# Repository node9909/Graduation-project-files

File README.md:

# Graduation internship report attachments (HD-SEMG system ADS1298)
 THis folder includes: Hardware files, software files, python application, MATLAB and report, design was to build a protable and wireless HD-SEMG aquisition system for my graduation internship of my electrical engineering degree at Hogeschool Rotterdam, the internship took place at Bio-engineering.pl in Wroclaw.

 The hypothesis of the project was ”Can the AMAC performance level be improved in direct controlled (DC) myoelectric systems by exactly locating the location where the patient has the most amount of cover the agonist and antagonist of the residual limb during different hand gestures’’. The goal was to develop a device that can be used to confirm this hypothesis, the could be achieved by measuring the muscle potentials over the residual limb during different hand gestures (HD-SEMG recording)

 In the project multiple AFE were designed were presented (based on AD8232 adn INA333), the function of the AFE to amplify and filter the EMG signal. THe EMG channels were digitezed using the ADS1298. the ADC data is read from the ADS1298 via an Arduino DUE (SAM3X8E)/ STM32F4.A PC application was developed to visualize the data and verifiy certain system specification (CMRR, IRN and Gain). The Current design is capable of measuring up to 1kSps with the Arduino DUE and to >4kSps with the STM32F411, the problem with the STM32F4 is the the Python application and realterm cannot open the USB port (CDC) to read the data, but it can be open in Tera term. If anybody knows why I would be happy to know :) 

 If you would like to continue this project Idea, feel to contact me for more info about the future improvements or any other questions about the design of the project.

# Contact details
 If you have any questions about the project feel free to contract me at: okersten@gmail.com

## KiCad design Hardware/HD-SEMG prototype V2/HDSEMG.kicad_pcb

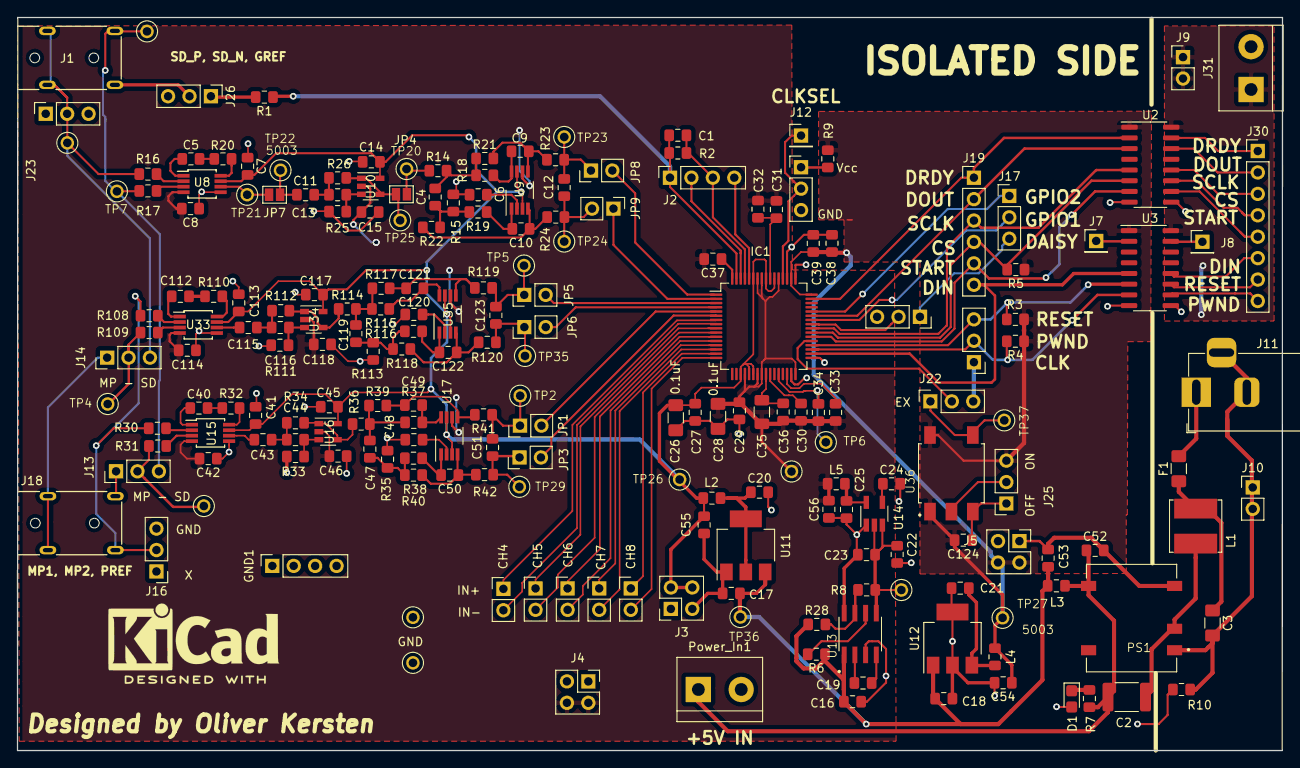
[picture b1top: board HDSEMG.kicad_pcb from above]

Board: 2 copper layers, 150.0 x 86.9 mm, 209 parts (0 on the bottom side), 140 nets.

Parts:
C1: 1M; C_0805_2012Metric_Pad1.15x1.40mm_HandSolder
C2: 470pF; Fuse_1812_4532Metric_Pad1.30x3.40mm_HandSolder
C3: 2.2uF; C_1206_3216Metric_Pad1.42x1.75mm_HandSolder
C4: 47nF; C_0805_2012Metric_Pad1.15x1.40mm_HandSolder
C5, C16, C22, C40, C112: 4.7uF; C_0805_2012Metric_Pad1.15x1.40mm_HandSolder
C6, C48, C120: 220nF; C_0805_2012Metric_Pad1.15x1.40mm_HandSolder
C7, C8, C14, C15, C41, C42, C45, C46, C113, C114, C117, C118: 100n; C_0805_2012Metric_Pad1.15x1.40mm_HandSolder
C9, C10, C50, C122: 2.2nF; C_0805_2012Metric_Pad1.15x1.40mm_HandSolder
C11, C13, C43, C44, C115, C116: 100nF; C_0805_2012Metric_Pad1.15x1.40mm_HandSolder
C12, C51, C123: 33nF; C_0805_2012Metric_Pad1.15x1.40mm_HandSolder
C17, C18, C19, C21, C27, C29, C30, C31, C33, C39: 1uF; C_0805_2012Metric_Pad1.15x1.40mm_HandSolder
C20, C23, C25: 2.2uF; C_0805_2012Metric_Pad1.15x1.40mm_HandSolder
C24, C124: 10nF; C_0805_2012Metric_Pad1.15x1.40mm_HandSolder
C26, C28: 0.1uF; C_1206_3216Metric_Pad1.42x1.75mm_HandSolder
C32: .1uF; C_0805_2012Metric_Pad1.15x1.40mm_HandSolder
C34: 22uF; C_0805_2012Metric_Pad1.15x1.40mm_HandSolder
C35: 10uF; C_1206_3216Metric
C36: 0.1u; C_0805_2012Metric_Pad1.15x1.40mm_HandSolder
C37: 1nF; C_0805_2012Metric_Pad1.15x1.40mm_HandSolder
C38: 0.1uF; C_0805_2012Metric_Pad1.15x1.40mm_HandSolder
C47, C119: 47n; C_0805_2012Metric_Pad1.15x1.40mm_HandSolder
C49, C121: 2.2n; C_0805_2012Metric_Pad1.15x1.40mm_HandSolder
C52, C53, C54, C55, C56: 10uF; C_0805_2012Metric_Pad1.15x1.40mm_HandSolder
CH4, CH5, CH6, CH7, CH8: Conn_01x02; PinHeader_1x02_P2.54mm_Vertical
D1: LED; D_0805_2012Metric_Castellated
F1: Fuse; Fuse_1206_3216Metric_Pad1.42x1.75mm_HandSolder
GND1: Conn_02x02_Counter_Clockwise; PinSocket_1x04_P2.54mm_Vertical
IC1: ADS1298_By_Oliver; TQFP-64_10x10mm_P0.5mm
J1, J18: AUDIO_JACK_By_OLIVER; MX387GL
J2: Conn_01x04; PinSocket_1x04_P2.54mm_Vertical
J3, J4, J5: Conn_02x02_Counter_Clockwise; PinSocket_2x02_P2.54mm_Vertical
J7, J8, J12: Conn_01x01; PinHeader_1x01_P2.54mm_Vertical
J9, J10: Conn_01x02; PinHeader_1x02_P2.54mm_Vertical
J11: Barrel_Jack_Switch; BarrelJack_Horizontal
J13, J14, J15, J16, J17, J24, J26: Conn_01x03; PinHeader_1x03_P2.54mm_Vertical
J19: Conn_01x06; PinHeader_1x06_P2.54mm_Vertical
J21, J22, J23, J25: Conn_01x03; PinSocket_1x03_P2.54mm_Vertical
J30: Conn_01x08; PinHeader_1x08_P2.54mm_Vertical
J31: Screw_Terminal_01x02; TerminalBlock_bornier-2_P5.08mm
JP1, JP3, JP5, JP6, JP8, JP9: Jumper; PinHeader_1x02_P2.54mm_Vertical
JP4, JP7: Jumper; SolderJumper-2_P1.3mm_Open_Pad1.0x1.5mm
L1: 10uH; L_Bourns_SRN6045TA
L2, L3, L4, L5: INDUCTOR; L_0805_2012Metric_Pad1.15x1.40mm_HandSolder
PS1: R2S-1205; CONV_R2S-1205
Power_In1: Screw_Terminal_01x02; TerminalBlock_bornier-2_P5.08mm
R1, R28: 100k; R_0805_2012Metric_Pad1.15x1.40mm_HandSolder
R2: 1.5nF; R_0805_2012Metric_Pad1.15x1.40mm_HandSolder
R3, R4, R5: 10K; R_0805_2012Metric_Pad1.15x1.40mm_HandSolder
R6, R7, R9: 10k; R_0805_2012Metric_Pad1.15x1.40mm_HandSolder
R8: 50k; R_0805_2012Metric_Pad1.15x1.40mm_HandSolder
R10: 0R; R_0805_2012Metric_Pad1.15x1.40mm_HandSolder
R14, R15, R35, R36, R113, R114: 1.1k; R_0805_2012Metric_Pad1.15x1.40mm_HandSolder
R16, R17, R30, R31, R108, R109: 51k; R_0805_2012Metric_Pad1.15x1.40mm_HandSolder
R18, R19, R37, R38, R115, R116: 5.6k; R_0805_2012Metric_Pad1.15x1.40mm_HandSolder
R20, R32, R110: 4300R; R_0805_2012Metric_Pad1.15x1.40mm_HandSolder
R21, R22, R39, R40, R117, R118: 11k; R_0805_2012Metric_Pad1.15x1.40mm_HandSolder
R23, R24, R41, R42, R119, R120: 50R; R_0805_2012Metric_Pad1.15x1.40mm_HandSolder
R25, R34, R112: 220k; R_0805_2012Metric_Pad1.15x1.40mm_HandSolder
R26: 110k; R_0805_2012Metric_Pad1.15x1.40mm_HandSolder
R33, R111: 430k; R_0805_2012Metric_Pad1.15x1.40mm_HandSolder
TP1, TP3, TP4, TP6, TP7, TP11, TP12, TP13, TP14, TP20, TP21, TP22, TP23, TP24, TP25, TP26, TP27, TP28, TP29, TP35, TP36, TP37: 5003; keystone_PCB_TEST_PIN
TP2, TP5: 5003; TPCW51D250H460P
U2, U3: Si8663; SOIC-16_3.9x9.9mm_P1.27mm
U8, U15, U33: INA333AIDGKR; MSOP-8_3x3mm_P0.65mm
U9, U17, U35: THS4521IDGKT; VSSOP-8_3.0x3.0mm_P0.65mm
U10, U16, U34: OPA333xxDBV; SOT-23-5
U11: TLV1117-25; SOT-223-3_TabPin2
U12: MCP1825S; SOT-223-3_TabPin2
U13: MAX889TESA+; SOIC127P600X175-8N
U14: TPS72325; SOT-23-5_HandSoldering
U36: 357LB3CI002M0480; SOIC254P1016X460-5N

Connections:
+2V5: C7.2, C14.1, C26.1, C27.1, C41.2, C45.1, C55.1, C113.2, C117.1, IC1.19, IC1.21, IC1.22, IC1.54, IC1.56, IC1.59, J3.3, J3.4, L2.2, TP26.1, U8.7, U9.3, U9.7, U10.5, U15.7, U16.5, U17.3, U17.7, U33.7, U34.5, U35.3, U35.7
+3V3: J9.1, J9.2, J31.1, U2.16, U3.16
+3_3V: C38.1, C39.1, C54.1, C124.2, IC1.48, IC1.50, J5.3, J5.4, J25.3, L4.2, R3.1, R4.1, R5.1, R9.1, TP27.1, U2.1, U3.1, U36.1, U36.6
+5V: C2.1, C52.1, L3.2, PS1.5, Power_In1.1, R7.1
-2V5: C8.2, C15.1, C28.1, C29.1, C30.2, C31.2, C32.2, C33.2, C34.2, C35.2, C36.2, C37.2, C42.2, C46.1, C56.1, C114.2, C118.1, IC1.20, IC1.23, IC1.24, IC1.32, IC1.53, IC1.57, IC1.58, J4.3, J4.4, L5.2, TP28.1, U8.4, U9.6, U10.2, U15.4, U16.2, U17.6, U33.4, U34.2, U35.6
/ADS1298 AFE in DUE out/EX_CLK_SIG: J22.1, TP37.1, U36.4
/Alternative Desing 1.3/low_pass_out: JP4.1, R26.1, TP25.1, U10.1, U10.4
/Input two/IN+3: J13.2, R31.2, TP3.1
/Power supply circuit/Power_IN: C16.1, C17.1, C18.1, C53.1, L3.1, R6.1, R28.1, TP36.1, U11.3, U12.1, U13.1
/sheet5DE654DA/IN+3: J14.2, R109.2, TP4.1
CHA_SD: J1.3, J13.3, R17.2, TP7.1, TP11.1
CHA_SD_N: J1.2, J14.3, J23.2, R16.2, TP12.1
CHB_MP: J14.1, J18.2
CHC_MP: J13.1, J18.3
CLK: J15.1, J22.3
CLKSEL: IC1.52, J12.1, J24.2
CS: IC1.39, J19.4, R5.2, U2.6
DAISY_CON_1: J17.3, J21.1
DGND: C6.2, C7.1, C8.1, C14.2, C15.2, C16.2, C17.2, C18.2, C20.2, C21.2, C22.2, C23.2, C24.2, C25.2, C26.2, C27.2, C28.2, C29.2, C38.2, C39.2, C41.1, C42.1, C45.2, C46.2, C48.2, C52.2, C53.2, C54.2, C55.2, C56.2, C113.1, C114.1, C117.2, C118.2, C120.2, C124.1, D1.2, GND1.1, GND1.2, GND1.3, GND1.4, IC1.31, IC1.33, IC1.49, IC1.51, J3.1, J3.2, J4.1, J4.2, J5.1, J5.2, J16.3, J21.3, J23.3, J24.3, J25.1, J26.3, PS1.4, Power_In1.2, R10.2, R15.1, R25.1, R33.1, R35.1, R111.1, R113.1, TP13.1, TP14.1, U2.8, U3.8, U8.5, U11.1, U12.2, U13.3, U13.8, U14.1, U15.5, U33.5, U36.3
DIN: IC1.34, J19.6, U3.5
DOUT: IC1.43, J19.2, U2.3
DRDY: IC1.47, J19.1, U2.2
GNDA: C3.2, J10.1, J10.2, J11.2, J11.3, J31.2, PS1.1, R10.1, U2.9, U3.9
GPIO_1: IC1.42, J17.2
GPIO_2: IC1.44, J17.1
IN1N: IC1.2, JP9.1
IN1P: IC1.1, JP8.2
IN2N: IC1.4, JP6.2
IN2P: IC1.3, JP5.2
IN3N: IC1.6, JP3.2
IN3P: IC1.5, JP1.2
IN4N: CH4.2, IC1.8
IN4P: CH4.1, IC1.7
IN5N: CH5.2, IC1.10
IN5P: CH5.1, IC1.9
IN6N: CH6.2, IC1.12
IN6P: CH6.1, IC1.11
IN7N: CH7.2, IC1.14
IN7P: CH7.1, IC1.13
IN8N: CH8.2, IC1.16
IN8P: CH8.1, IC1.15
ISO_CS: J30.4, U2.11
ISO_DIN: J30.6, U3.12
ISO_DOUT: J30.2, U2.14
ISO_DRDY: J30.1, U2.15
ISO_PWDN: J30.8, U3.10
ISO_RESET: J30.7, U3.11
ISO_SCLK: J30.3, U2.12
ISO_START: J30.5, U2.10
unnamed: C2.2, L1.2, PS1.2
unnamed: C3.1, F1.1, L1.1
unnamed: C4.1, R15.2, R19.1, R22.1
unnamed: C4.2, R14.2, R18.1, R21.1
unnamed: C5.1, U8.1
unnamed: C5.2, R20.2
unnamed: C6.1, U9.2
unnamed: C9.1, R21.2, R23.2, U9.5
unnamed: C9.2, R18.2, U9.8
unnamed: C10.1, R22.2, R24.1, U9.4
unnamed: C10.2, R19.2, U9.1
unnamed: C11.1, JP7.2, TP22.1
unnamed: C11.2, C13.1, R26.2
unnamed: C12.1, JP8.1, R23.1, TP23.1
unnamed: C12.2, JP9.2, R24.2, TP24.1
unnamed: C13.2, R25.2, U10.3
unnamed: C19.1, U13.2
unnamed: C19.2, U13.4
unnamed: C20.1, L2.1, U11.2
unnamed: C21.1, L4.1, U12.3
unnamed: C22.1, C23.1, R8.1, TP1.1, U13.5, U14.2, U14.3
unnamed: C24.1, U14.4
unnamed: C25.1, L5.1, U14.5
unnamed: C40.1, U15.1
unnamed: C40.2, R32.2
unnamed: C43.1, U15.6
unnamed: C43.2, C44.1, R34.2
unnamed: C44.2, R33.2, U16.3
unnamed: C47.1, R35.2, R38.1, R40.1
unnamed: C47.2, R36.2, R37.1, R39.1
unnamed: C48.1, U17.2
unnamed: C49.1, R39.2, R41.2, U17.5
unnamed: C49.2, R37.2, U17.8
unnamed: C50.1, R40.2, R42.1, U17.4
unnamed: C50.2, R38.2, U17.1
unnamed: C51.1, JP1.1, R41.1, TP2.1
unnamed: C51.2, JP3.1, R42.2, TP29.1
unnamed: C112.1, U33.1
unnamed: C112.2, R110.2
unnamed: C115.1, U33.6
unnamed: C115.2, C116.1, R112.2
unnamed: C116.2, R111.2, U34.3
unnamed: C119.1, R113.2, R116.1, R118.1
unnamed: C119.2, R114.2, R115.1, R117.1
unnamed: C120.1, U35.2
unnamed: C121.1, R117.2, R119.2, U35.5
unnamed: C121.2, R115.2, U35.8
unnamed: C122.1, R118.2, R120.1, U35.4
unnamed: C122.2, R116.2, U35.1
unnamed: C123.1, JP5.1, R119.1, TP5.1
unnamed: C123.2, JP6.1, R120.2, TP35.1
unnamed: D1.1, R7.2
unnamed: F1.2, J11.1
unnamed: IC1.37, J22.2
unnamed: IC1.41, J21.2
unnamed: J1.1, J26.2
unnamed: J7.1, U3.2
unnamed: J8.1, U3.15
unnamed: J24.1, R9.2
unnamed: J25.2, U36.2
unnamed: J26.1, R1.2
unnamed: JP4.2, R14.1, TP20.1
unnamed: JP7.1, TP21.1, U8.6
unnamed: R6.2, U13.6
unnamed: R16.1, U8.2
unnamed: R17.1, U8.3
unnamed: R20.1, U8.8
unnamed: R8.2, R28.2, U13.7
unnamed: R30.1, U15.2
unnamed: R31.1, U15.3
unnamed: R32.1, U15.8
unnamed: R34.1, R36.1, U16.1, U16.4
unnamed: R108.1, U33.2
unnamed: R109.1, U33.3
unnamed: R110.1, U33.8
unnamed: R112.1, R114.1, U34.1, U34.4
PREF: J16.2, J18.1, R30.2, R108.2
PWDN: IC1.35, J15.2, R4.2, U3.7
RESET: IC1.36, J15.3, R3.2, U3.6
RLDIN1: IC1.62, J2.2
RLDINV: C1.2, IC1.61, J2.3, R2.1
RLDOUT1: C1.1, IC1.63, J2.1, R1.1, R2.2
RLD_REF1: IC1.60, J2.4
SCLK: IC1.40, J19.3, U2.5
START: IC1.38, J19.5, U2.7
VCAP1_1: C34.1, IC1.28, TP6.1
VCAP2_1: C33.1, IC1.30
VCAP3_1: C31.1, C32.1, IC1.55
VCAP4_1: C30.1, IC1.26
VREFP1: C35.1, C36.1, IC1.25
WTC_1: C37.1, IC1.64

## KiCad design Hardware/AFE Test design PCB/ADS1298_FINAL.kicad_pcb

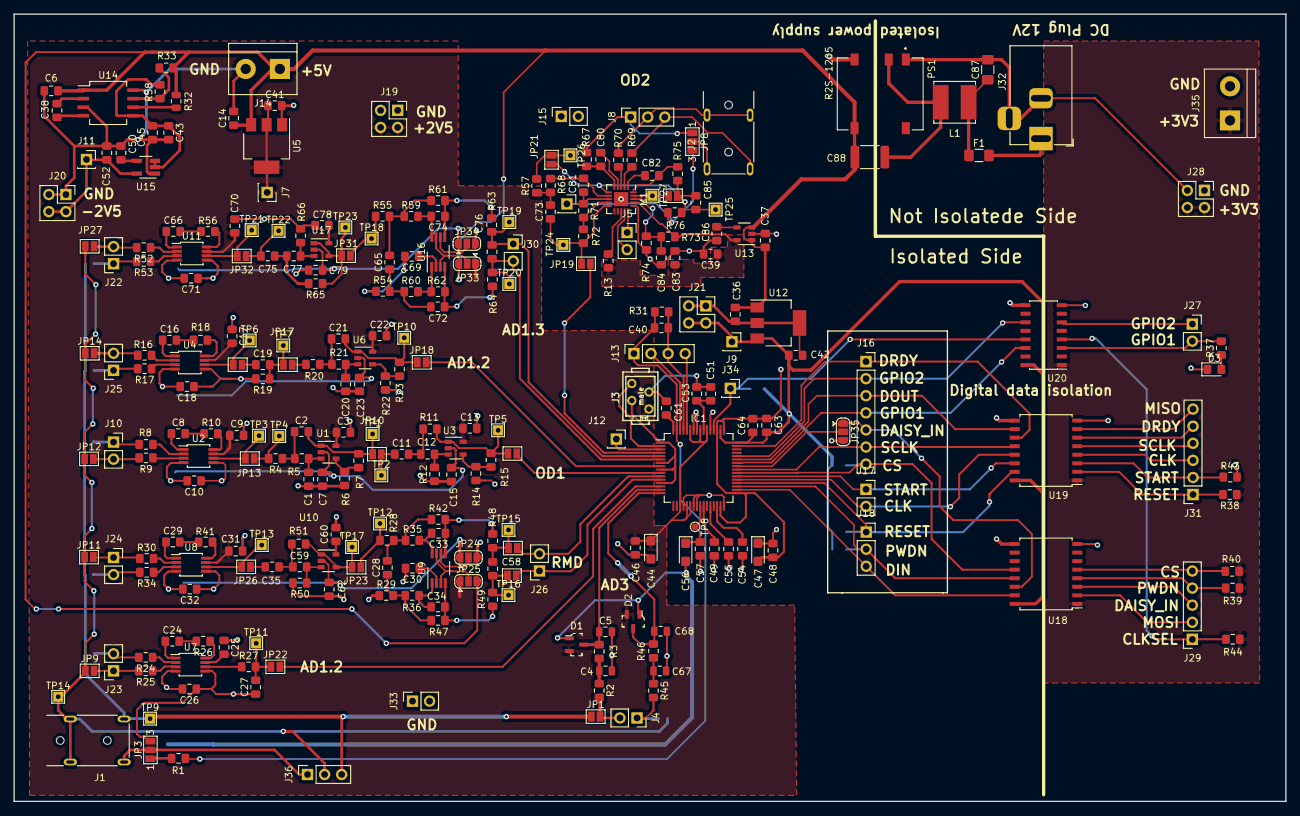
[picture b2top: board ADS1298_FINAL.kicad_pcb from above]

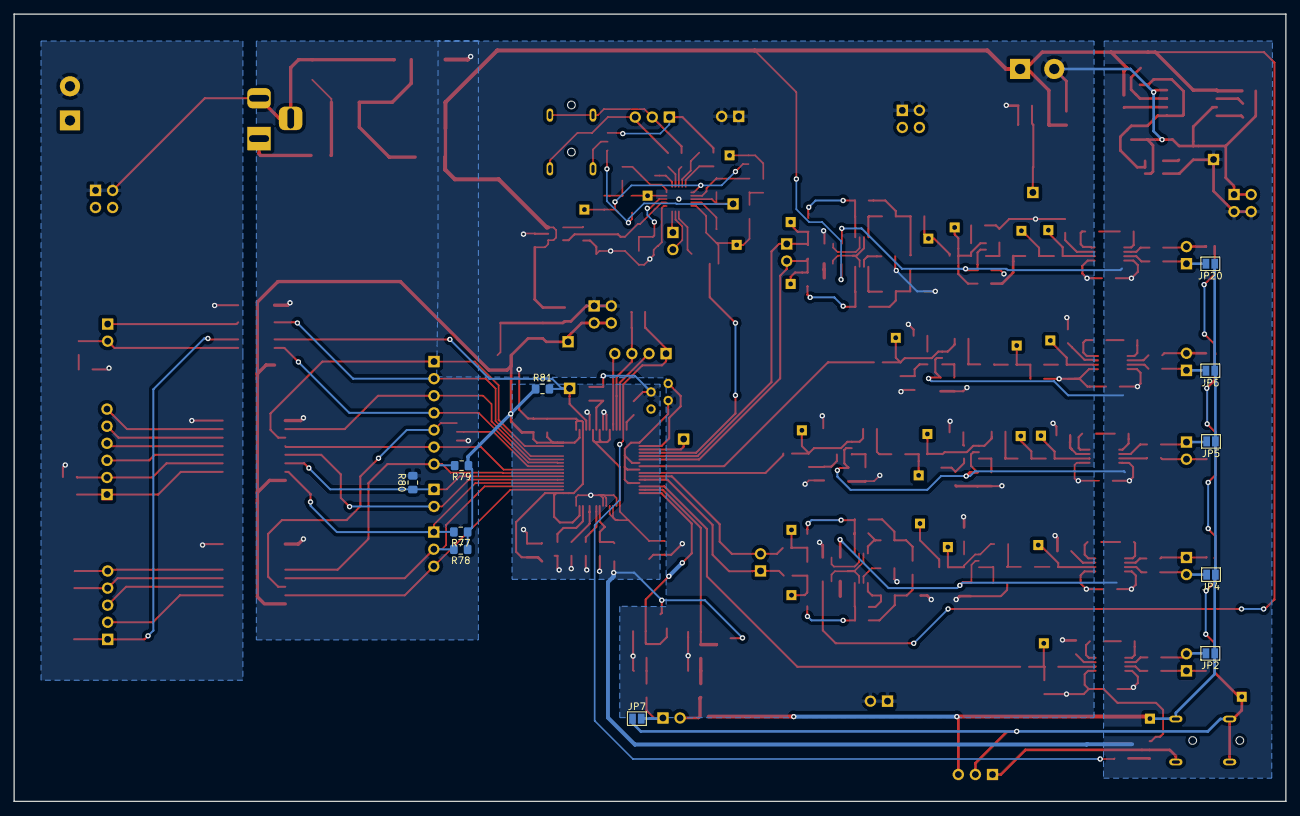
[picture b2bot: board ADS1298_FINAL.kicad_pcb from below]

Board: 2 copper layers, 189.0 x 117.0 mm, 295 parts (11 on the bottom side), 187 nets.

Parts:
C1, C2, C20, C21, C35, C59, C75, C77: 4.7nF; C_0805_2012Metric_Pad1.15x1.40mm_HandSolder
C3, C7, C9, C10, C13, C15, C17, C18, C19, C22, C23, C25, C26, C27, C28, C30, C31, C32, C33, C34, C58, C60, C62, C65, C69, C70, C71, C72, C74, C76, C78, C79: 100n; C_0805_2012Metric_Pad1.15x1.40mm_HandSolder
C4, C5, C67, C68: 47pF; C_0805_2012Metric
C6, C43: 4.7uF; C_0805_2012Metric_Pad1.15x1.40mm_HandSolder
C8, C16, C24, C29: 10uF; C_0805_2012Metric_Pad1.15x1.40mm_HandSolder
C11, C12, C50, C86: 10nF; C_0805_2012Metric_Pad1.15x1.40mm_HandSolder
C14, C36, C37, C38, C41, C42, C49, C51, C54, C64, C66: 1uF; C_0805_2012Metric_Pad1.15x1.40mm_HandSolder
C39, C45, C52: 2.2uF; C_0805_2012Metric_Pad1.15x1.40mm_HandSolder
C40: 1M; C_0805_2012Metric_Pad1.15x1.40mm_HandSolder
C44: 10uF; CP_EIA-3216-12_Kemet-S
C46, C48, C57: 0.1u; C_0805_2012Metric_Pad1.15x1.40mm_HandSolder
C47, C56: 10uF; CP_EIA-3216-10_Kemet-I
C53: .1uF; C_0805_2012Metric_Pad1.15x1.40mm_HandSolder
C55: 22uF; C_0805_2012Metric_Pad1.15x1.40mm_HandSolder
C61, C73, C80, C81: 1nF; C_0805_2012Metric_Pad1.15x1.40mm_HandSolder
C63: 0.1uF; C_0805_2012Metric_Pad1.15x1.40mm_HandSolder
C82, C85: 4700nF; C_0805_2012Metric_Pad1.15x1.40mm_HandSolder
C83, C84: 100nF; C_0805_2012Metric_Pad1.15x1.40mm_HandSolder
C87: 2.2uF; C_1206_3216Metric_Pad1.42x1.75mm_HandSolder
C88: 470pF; Fuse_1812_4532Metric_Pad1.30x3.40mm_HandSolder
D1, D2: D_Schottky_x2_Serial_AKC; SOT-23-3
D3: LED; LED_0805_2012Metric_Pad1.15x1.40mm_HandSolder
F1: Fuse; Fuse_1206_3216Metric_Pad1.42x1.75mm_HandSolder
IC1: ADS1298_By_Oliver; TQFP-64_10x10mm_P0.5mm
J1, J2: AUDIO_JACK_By_OLIVER; MX387GL
J3: external header 2; 0-215464-4_TH_4-pin_male
J4, J5, J10, J15, J17, J22, J23, J24, J25, J26, J27, J30, J33: Conn_01x02; PinSocket_1x02_P2.54mm_Vertical
J6, J7, J9, J11, J12, J34: Conn_01x01; PinSocket_1x01_P2.54mm_Vertical
J8, J18, J36: Conn_01x03; PinSocket_1x03_P2.54mm_Vertical
J13: Conn_01x04; PinSocket_1x04_P2.54mm_Vertical
J14, J35: Screw_Terminal_01x02; TerminalBlock_bornier-2_P5.08mm
J16: Conn_01x07; PinSocket_1x07_P2.54mm_Vertical
J19, J20, J21, J28: Conn_02x02_Counter_Clockwise; PinSocket_2x02_P2.54mm_Vertical
J29: Conn_01x05; PinSocket_1x05_P2.54mm_Vertical
J31: Conn_01x06; PinSocket_1x06_P2.54mm_Vertical
J32: Barrel_Jack_Switch; BarrelJack_Horizontal
JP1, JP2, JP4, JP5, JP6, JP7, JP9, JP11, JP12, JP14, JP19, JP20, JP27: SolderJumper_2_Open; SolderJumper-2_P1.3mm_Open_Pad1.0x1.5mm
JP3, JP8: Jumper_3_Open; SolderJumper-3_P1.3mm_Open_Pad1.0x1.5mm_NumberLabels
JP10, JP13, JP15, JP16, JP17, JP18, JP22, JP23, JP26, JP28, JP30, JP31, JP32: Jumper; SolderJumper-2_P1.3mm_Open_Pad1.0x1.5mm
JP21, JP29: Jumper_2_Open; SolderJumper-2_P1.3mm_Open_Pad1.0x1.5mm
JP24, JP25, JP33, JP34, JP35: Jumper_3_Open; SolderJumper-3_P1.3mm_Open_RoundedPad1.0x1.5mm
L1: 10uH; L_Bourns_SRN6045TA
M1: AD8232; LFCSP-20-1EP_4x4mm_P0.5mm_EP2.1x2.1mm
PS1: R2S-1205; CONV_R2S-1205
R1, R8, R9, R16, R17, R24, R25, R30, R33, R34, R52, R53: 100k; R_0805_2012Metric_Pad1.15x1.40mm_HandSolder
R2, R3, R45, R46: 2.1k; R_0805_2012Metric_Pad1.15x1.40mm_HandSolder
R4: 47k; R_0805_2012Metric_Pad1.15x1.40mm_HandSolder
R5: 91k; R_0805_2012Metric_Pad1.15x1.40mm_HandSolder
R6, R39, R78: 10K; R_0805_2012Metric_Pad1.15x1.40mm_HandSolder
R7, R13, R14, R15, R22, R38, R43, R44, R71, R77, R80, R81: 10k; R_0805_2012Metric_Pad1.15x1.40mm_HandSolder
R10, R18, R26, R41: 1300R; R_0805_2012Metric_Pad1.15x1.40mm_HandSolder
R11: 1.8M; R_0805_2012Metric_Pad1.15x1.40mm_HandSolder
R12: 1.3M; R_0805_2012Metric_Pad1.15x1.40mm_HandSolder
R19, R27, R37: 1K; R_0805_2012Metric_Pad1.15x1.40mm_HandSolder
R20, R50: 36k; R_0805_2012Metric_Pad1.15x1.40mm_HandSolder
R21, R28, R29, R35, R36, R42, R47, R48, R49, R51, R54, R55, R59, R60, R61, R62, R63, R64: 130k; R_0805_2012Metric_Pad1.15x1.40mm_HandSolder
R23, R72: 30k; R_0805_2012Metric_Pad1.15x1.40mm_HandSolder
R31: 1.5nF; R_0805_2012Metric_Pad1.15x1.40mm_HandSolder
R32: 10k; R_0805_2012Metric
R40, R79: 100K; R_0805_2012Metric_Pad1.15x1.40mm_HandSolder
R56: 20k; R_0805_2012Metric_Pad1.15x1.40mm_HandSolder
R57: 160k; R_0805_2012Metric_Pad1.15x1.40mm_HandSolder
R58: 50k; R_0805_2012Metric_Pad1.15x1.40mm_HandSolder
R65, R66: R; R_0805_2012Metric_Pad1.15x1.40mm_HandSolder
R67: 390k; R_0805_2012Metric_Pad1.15x1.40mm_HandSolder
R68: 620k; R_0805_2012Metric_Pad1.15x1.40mm_HandSolder
R69, R70: 180k; R_0805_2012Metric_Pad1.15x1.40mm_HandSolder
R73, R74: 10M; R_0805_2012Metric_Pad1.15x1.40mm_HandSolder
R75: 340k; R_0805_2012Metric_Pad1.15x1.40mm_HandSolder
R76: 3.4k; R_0805_2012Metric_Pad1.15x1.40mm_HandSolder
TP1, TP2, TP3, TP4, TP5, TP6, TP7, TP9, TP10, TP11, TP12, TP13, TP14, TP15, TP16, TP17, TP18, TP19, TP20, TP21, TP22, TP23, TP24, TP25, TP26, TP27: TestPoint; TestPoint_THTPad_1.5x1.5mm_Drill0.7mm
TP8: TestPoint; TestPoint_Pad_D1.0mm
U1, U3, U6, U10, U17: OPA333xxDBV; SOT-23-5
U2, U4, U7, U8, U11: INA333AIDGKR; MSOP-8_3x3mm_P0.65mm
U5: TLV1117-25; SOT-223-3_TabPin2
U9, U16: THS4521IDGKT; VSSOP-8_3.0x3.0mm_P0.65mm
U12: MCP1825S; SOT-223-3_TabPin2
U13: LP2985-3.5; SOT-23-5
U14: MAX889T; SO-8_5.3x6.2mm_P1.27mm
U15: TPS72325; SOT-23-5_HandSoldering
U18, U19: Si8662; SOIC-16W_7.5x10.3mm_P1.27mm
U20: Si8606; SOIC-16_3.9x9.9mm_P1.27mm

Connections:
+2V5: C3.1, C9.2, C13.1, C17.2, C22.1, C25.2, C31.2, C41.1, C44.1, C46.1, C60.1, C70.2, C78.1, D1.2, D2.2, IC1.19, IC1.21, IC1.22, IC1.54, IC1.56, IC1.59, J3.1, J7.1, J19.3, J19.4, JP25.1, JP33.1, U1.5, U2.7, U3.5, U4.7, U5.2, U6.5, U7.7, U8.7, U10.5, U11.7, U17.5
+3V3: J28.3, J28.4, J35.1, R38.1, R39.1, R40.1, R44.1, U18.1, U19.1, U20.1
+3V5: C39.1, C83.2, M1.17, R13.2, R73.1, U13.5
+3_3V: C42.1, C63.1, C64.1, IC1.48, IC1.50, J9.1, J21.3, J21.4, R77.1, R78.1, R79.1, R81.1, U12.3, U18.16, U19.16, U20.16
+5V: C6.1, C14.1, C36.1, C37.1, C88.1, J14.1, JP25.3, JP33.3, PS1.5, R32.1, R33.1, U5.3, U12.1, U13.1, U13.3, U14.1
-2V5: C7.2, C10.2, C15.1, C18.2, C23.1, C26.2, C32.2, C47.1, C48.1, C49.2, C51.2, C52.1, C53.2, C54.2, C55.2, C56.2, C57.2, C61.2, C62.1, C71.2, C79.1, D1.1, D2.1, IC1.20, IC1.23, IC1.24, IC1.32, IC1.53, IC1.57, IC1.58, J3.3, J11.1, J20.3, J20.4, JP24.1, JP34.1, U1.2, U2.4, U3.2, U4.4, U6.2, U7.4, U8.4, U10.2, U11.4, U15.5, U17.2
/Alternative Desing 1.3/low_pass_out: JP23.1, R51.1, TP17.1, U10.1, U10.4
/Original design 1/INA_OUT: JP13.2, R4.2, TP4.1
/Schematic marelini/low_pass_out_m: JP31.1, R65.1, TP23.1, U17.1, U17.4
/sheet794AF31F/EMG_OUT: C73.1, JP19.1, M1.10, R72.2, TP24.1
/sheet794AF31F/SDN_MCU: M1.13, R13.1
AD-DC1: J5.2, M1.14
AGND: C87.2, D3.1, J28.1, J28.2, J32.2, J32.3, J35.2, PS1.1, R43.2, U18.8, U19.8, U20.8
CLK: IC1.37, J17.2, U19.13
CLKSEL: IC1.52, J34.1, R81.2, U20.13
CLKSEL_ISO: J29.1, R44.2, U20.4
CLK_ISO: J31.3, U19.4
CS: IC1.39, J16.7, R79.2, U18.12
CS_ISO: J29.5, R40.2, U18.5
DAISY_CON_1: J16.5, JP35.1, U18.14
DAISY_CON_1_ISO: J29.3, U18.3
DGND: C1.1, C3.2, C4.2, C5.2, C6.2, C7.1, C9.1, C10.1, C13.2, C14.2, C15.2, C17.1, C18.1, C20.1, C22.2, C23.2, C25.1, C26.1, C27.1, C30.2, C31.1, C32.1, C36.2, C37.2, C39.2, C41.2, C42.2, C43.2, C44.2, C45.2, C46.2, C47.2, C48.2, C50.2, C52.2, C60.2, C62.2, C63.2, C64.2, C67.2, C68.2, C69.2, C70.1, C71.1, C78.2, C79.2, C83.1, C84.2, C86.2, IC1.1, IC1.7, IC1.9, IC1.13, IC1.31, IC1.33, IC1.49, IC1.51, J3.2, J14.2, J15.1, J15.2, J19.1, J19.2, J20.1, J20.2, J21.1, J21.2, J33.1, J33.2, JP3.3, JP24.3, JP34.3, JP35.3, M1.16, M1.21, PS1.4, R6.1, R12.1, R14.1, R19.2, R22.1, R29.1, R50.1, R54.1, R66.2, R74.1, R80.2, U2.5, U4.5, U5.1, U7.5, U8.5, U11.5, U12.2, U13.2, U14.3, U14.8, U15.1, U18.9, U19.9, U20.9
DIN: IC1.34, J18.3, U18.15
DOUT: IC1.43, J16.3, U19.10
DRDY: IC1.47, J16.1, U19.11
DRDY_ISO: J31.5, U19.6
DRL3: J8.1, JP8.1, R67.2
FR1: J5.1, M1.15
GPIO_1: IC1.42, J16.4, U20.14
GPIO_1_ISO: J27.2, R37.2, U20.3
GPIO_2: IC1.44, J16.2, U20.11
GPIO_2_ISO: J27.1, U20.6
IN1N: C68.1, D2.3, IC1.16, R46.1
IN1NI: J4.1, JP7.2, R45.2
IN1P: C5.1, D1.3, IC1.15, R3.1
IN1PI: J4.2, JP1.2, R2.2
IN2: IC1.14, JP22.2
IN3N: IC1.11, J26.2, JP28.2
IN3P: IC1.12, J26.1, JP30.1
IN4: IC1.10, JP15.2
IN5: IC1.8, JP18.2
IN6N: C76.2, IC1.6, J30.2, R64.2, TP20.1
IN6P: C76.1, IC1.5, J30.1, R63.1, TP19.1
IN7: IC1.4, JP19.2
IN8: IC1.2, J3.4
IN+2: J23.2, JP2.2, R24.2
IN+3: J24.2, JP4.2, R34.2
IN+4: J10.1, JP5.2, R8.2
IN+5: J25.1, JP6.2, R17.2
IN+8: J2.2, J8.2, R70.2
IN+9: J22.1, JP20.2, R53.2
IN-2: J23.1, JP9.2, R25.2
IN-3: J24.1, JP11.2, R30.2
IN-4: J10.2, JP12.2, R9.2
IN-5: J25.2, JP14.2, R16.2
IN-8: J2.3, J8.3, R69.2
IN-9: J22.2, JP27.2, R52.2
MISO_ISO: J31.6, U19.7
MOSI_ISO: J29.2, U18.2
unnamed: C1.2, R5.1, U1.3
unnamed: C2.1, R4.1, R5.2
unnamed: C2.2, JP10.1, R7.2, TP1.1, U1.1
unnamed: C4.1, R2.1, R3.2
unnamed: C8.1, U2.1
unnamed: C8.2, R10.2
unnamed: C11.1, JP10.2, TP2.1
unnamed: C11.2, C12.2, R11.2
unnamed: C12.1, R12.2, U3.3
unnamed: C16.1, U4.1
unnamed: C16.2, R18.2
unnamed: C19.1, JP16.2
unnamed: C19.2, JP17.1, R19.1, TP7.1
unnamed: C20.2, R21.1, U6.3
unnamed: C21.1, R20.1, R21.2
unnamed: C21.2, JP18.1, R23.2, TP10.1, U6.1
unnamed: C24.1, U7.1
unnamed: C24.2, R26.2
unnamed: C27.2, JP22.1, R27.2, TP11.1
unnamed: C28.1, R29.2, R36.1, R47.1
unnamed: C28.2, R28.2, R35.1, R42.1
unnamed: C29.1, U8.1
unnamed: C29.2, R41.2
unnamed: C30.1, U9.2
unnamed: C33.1, R42.2, R48.2, U9.5
unnamed: C33.2, R35.2, U9.8
unnamed: C34.1, R47.2, R49.1, U9.4
unnamed: C34.2, R36.2, U9.1
unnamed: C35.1, JP26.2
unnamed: C35.2, C59.1, R51.2
unnamed: C38.1, U14.2
unnamed: C38.2, U14.4
unnamed: C43.1, C45.1, R58.2, U14.5, U15.2, U15.3
unnamed: C50.1, U15.4
unnamed: C58.1, JP28.1, R48.1, TP15.1
unnamed: C58.2, JP30.2, R49.2, TP16.1
unnamed: C59.2, R50.2, U10.3
unnamed: C65.1, R54.2, R60.1, R62.1
unnamed: C65.2, R55.2, R59.1, R61.1
unnamed: C66.1, U11.1
unnamed: C66.2, R56.2
unnamed: C67.1, R45.1, R46.2
unnamed: C69.1, U16.2
unnamed: C72.1, R62.2, R64.1, U16.4
unnamed: C72.2, R60.2, U16.1
unnamed: C73.2, R57.1, R68.2
unnamed: C74.1, R61.2, R63.2, U16.5
unnamed: C74.2, R59.2, U16.8
unnamed: C75.1, JP32.2, TP22.1
unnamed: C75.2, C77.1, R65.2
unnamed: C77.2, R66.1, U17.3
unnamed: C80.1, M1.5, R67.1
unnamed: C80.2, M1.4
unnamed: C81.2, M1.7, R68.1
unnamed: C82.1, M1.20, R75.2
unnamed: C82.2, M1.1
unnamed: C84.1, M1.18, R73.2, R74.2
unnamed: C85.1, JP21.2, M1.6, R76.2, TP25.1
unnamed: C85.2, JP29.2, R75.1
unnamed: C86.1, U13.4
unnamed: C87.1, F1.1, L1.1
unnamed: C88.2, L1.2, PS1.2
unnamed: D3.2, R37.1
unnamed: F1.2, J32.1
unnamed: IC1.41, JP35.2
unnamed: J1.1, J36.1, JP3.2
unnamed: J1.2, J36.2, JP7.1, JP9.1, JP11.1, JP12.1, JP14.1, JP27.1, TP14.1
unnamed: J1.3, J36.3, JP1.1, JP2.1, JP4.1, JP5.1, JP6.1, JP20.1, TP9.1
unnamed: J2.1, JP8.2
unnamed: JP3.1, R1.2
unnamed: JP13.1, TP3.1, U2.6
unnamed: JP15.1, R11.1, R15.2, TP5.1, U3.1
unnamed: JP16.1, TP6.1, U4.6
unnamed: JP17.2, R20.2
unnamed: JP21.1, R57.2, TP26.1
unnamed: JP23.2, R28.1, TP12.1
unnamed: JP24.2, U9.6
unnamed: JP25.2, U9.3, U9.7
unnamed: JP26.1, TP13.1, U8.6
unnamed: JP29.1, M1.19, TP27.1
unnamed: JP31.2, R55.1, TP18.1
unnamed: JP32.1, TP21.1, U11.6
unnamed: JP33.2, U16.3, U16.7
unnamed: JP34.2, U16.6
unnamed: M1.2, R69.1
unnamed: M1.3, R70.1
unnamed: M1.9, R71.2, R72.1
unnamed: R6.2, R7.1, U1.4
unnamed: R8.1, U2.2
unnamed: R9.1, U2.3
unnamed: R10.1, U2.8
unnamed: R14.2, R15.1, U3.4
unnamed: R16.1, U4.2
unnamed: R17.1, U4.3
unnamed: R18.1, U4.8
unnamed: R22.2, R23.1, U6.4
unnamed: R24.1, U7.2
unnamed: R25.1, U7.3
unnamed: R26.1, U7.8
unnamed: R27.1, U7.6
unnamed: R30.1, U8.2
unnamed: R32.2, U14.6
unnamed: R33.2, R58.1, U14.7
unnamed: R34.1, U8.3
unnamed: R41.1, U8.8
unnamed: R52.1, U11.2
unnamed: R53.1, U11.3
unnamed: R56.1, U11.8
OFFSET_AD8232: IC1.3, J12.1
PWDN: IC1.35, J18.2, R78.2, U18.13
PWDN_ISO: J29.4, R39.2, U18.4
REF_OUT_AD8232: C81.1, J6.1, JP8.3, M1.8, R71.1, R76.1
RESET: IC1.36, J18.1, R77.2, U19.15
RESET_ISO: J31.1, R38.2, U19.2
RLDIN1: IC1.62, J13.2
RLDINV: C40.2, IC1.61, J13.3, R31.1
RLDOUT1: C40.1, IC1.63, J13.1, R1.1, R31.2
RLD_REF1: IC1.60, J13.4
SCLK: IC1.40, J16.6, U19.12
SCLK_ISO: J31.4, U19.5
START: IC1.38, J17.1, R80.1, U19.14
START_ISO: J31.2, R43.1, U19.3
VCAP1_1: C55.1, IC1.28
VCAP2_1: C54.1, IC1.30
VCAP3_1: C51.1, C53.1, IC1.55
VCAP4_1: C49.1, IC1.26
VREFP1: C56.1, C57.1, IC1.25, TP8.1
WTC_1: C61.1, IC1.64

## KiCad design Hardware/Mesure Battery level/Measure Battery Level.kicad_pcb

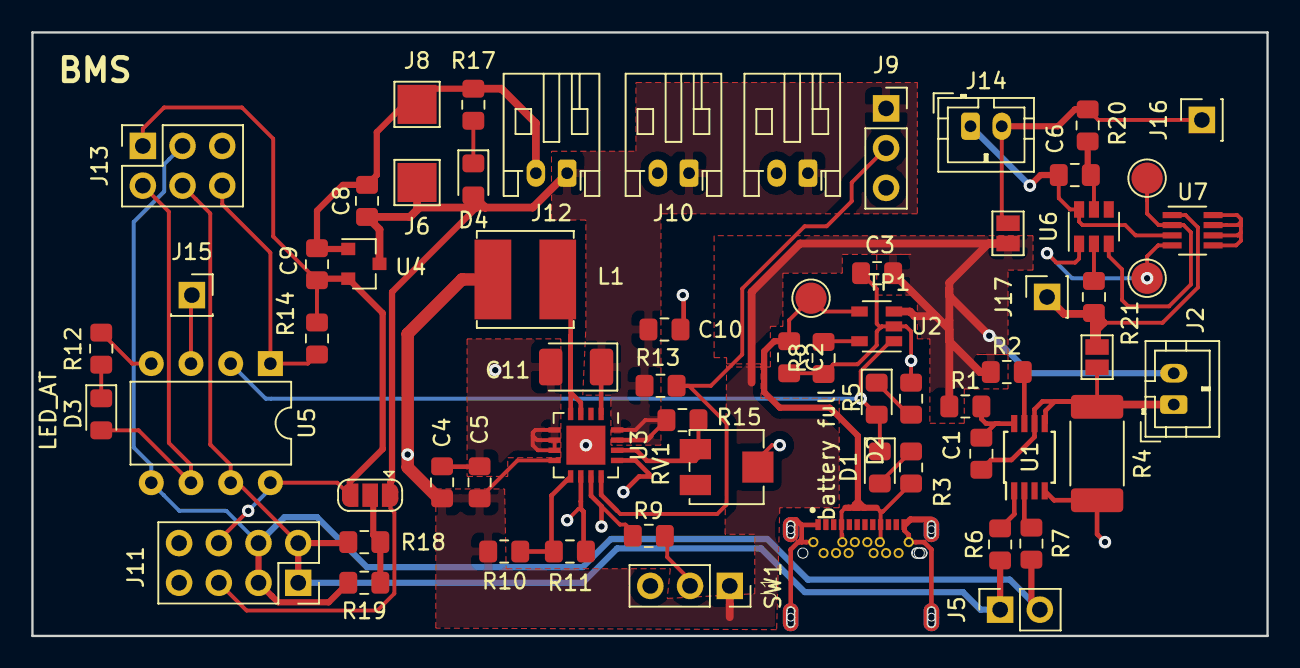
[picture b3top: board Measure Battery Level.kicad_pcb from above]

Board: 2 copper layers, 79.0 x 38.6 mm, 65 parts (0 on the bottom side), 36 nets.

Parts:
C1: 100nF; C_0805_2012Metric_Pad1.15x1.40mm_HandSolder
C2, C3, C4: 10uF; C_0805_2012Metric_Pad1.15x1.40mm_HandSolder
C5: 0.1uF; C_0805_2012Metric_Pad1.15x1.40mm_HandSolder
C6: C; C_0805_2012Metric_Pad1.15x1.40mm_HandSolder
C8, C9: 1uF; C_0805_2012Metric_Pad1.15x1.40mm_HandSolder
C10: 2.2uF; C_0805_2012Metric_Pad1.15x1.40mm_HandSolder
C11: 100UF(tan); CP_EIA-3528-12_Kemet-T_Pad1.50x2.35mm_HandSolder
D1: bat charging; LED_0805_2012Metric_Pad1.15x1.40mm_HandSolder
D2: battery full; LED_0805_2012Metric_Pad1.15x1.40mm_HandSolder
D3: LED_AT; LED_0805_2012Metric_Pad1.15x1.40mm_HandSolder
D4: LED; LED_0805_2012Metric_Pad1.15x1.40mm_HandSolder
J1: USB4065-XX-X_REVA; GCT_USB4065-XX-X_REVA
J2, J14: CONN_02JST-PTH-2; JST_PH_B2B-PH-K_1x02_P2.00mm_Vertical
J5: Debug header; PinSocket_1x02_P2.54mm_Vertical
J6: 5V; TestPoint_Pad_2.5x2.5mm
J7, J10, J12: POWER_OUT; JST_PH_S2B-PH-K_1x02_P2.00mm_Horizontal
J8: GND; TestPoint_Pad_2.5x2.5mm
J9: Conn_01x03; PinSocket_1x03_P2.54mm_Vertical
J11: Conn_02x04_Odd_Even; PinSocket_2x04_P2.54mm_Vertical
J13: Conn_02x03_Odd_Even; PinSocket_2x03_P2.54mm_Vertical
J15, J16, J17: Conn_01x01; PinSocket_1x01_P2.54mm_Vertical
JP1: Jumper_3_Open; SolderJumper-3_P1.3mm_Open_RoundedPad1.0x1.5mm
JP2, JP3: Jumper; SolderJumper-2_P1.3mm_Open_Pad1.0x1.5mm
L1: 6.8uH; L_Bourns_SRN6045TA
R1: 500R; R_0805_2012Metric_Pad1.15x1.40mm_HandSolder
R2: 1000R; R_0805_2012Metric_Pad1.15x1.40mm_HandSolder
R3, R5, R12, R17: 1K; R_0805_2012Metric_Pad1.15x1.40mm_HandSolder
R4: Rsns; R_2512_6332Metric_Pad1.52x3.35mm_HandSolder
R6, R7: 150R; R_0805_2012Metric_Pad1.15x1.40mm_HandSolder
R8: Charge Current; R_0805_2012Metric_Pad1.15x1.40mm_HandSolder
R9, R20, R21: R; R_0805_2012Metric_Pad1.15x1.40mm_HandSolder
R10: 1.8MR; R_0805_2012Metric_Pad1.15x1.40mm_HandSolder
R11: 330k; R_0805_2012Metric_Pad1.15x1.40mm_HandSolder
R13: 2MOhm; R_0805_2012Metric_Pad1.15x1.40mm_HandSolder
R14: 10K; R_0805_2012Metric_Pad1.15x1.40mm_HandSolder
R15: 1.8Mohm; R_0805_2012Metric_Pad1.15x1.40mm_HandSolder
R18, R19: 4.7K; R_0805_2012Metric_Pad1.15x1.40mm_HandSolder
RV1: R_POT_TRIM; Potentiometer_Bourns_3314J_Vertical
SW1: Switch_SW_SPDT; PinSocket_1x03_P2.54mm_Vertical
TP1, TP2, TP3: TestPoint; TestPoint_Pad_D2.0mm
U1: ds2745_oliver; TSSOP-8_3x3mm_P0.65mm
U2: MCP73831; SOT-23-5
U3: TPS61090; QFN-16-1EP_4x4mm_P0.65mm_EP2.5x2.5mm
U4: MCP1703A-3302_SOT23; SOT-23
U5: ATtiny85-20PU; DIP-8_W7.62mm
U6: AP9101C; SOT-23-6
U7: ECH8693R; TSOT-23-8

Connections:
+3V3: C9.1, J11.6, J13.1, JP1.3, R14.1, U4.2, U5.8
+5V: C8.1, C10.1, C11.1, D4.2, J6.1, J7.1, J9.1, J10.1, J11.5, J12.1, JP1.1, R13.1, R15.1, U3.1, U3.15, U3.16, U4.3
+BATT: C3.1, C4.1, C5.1, J2.2, JP2.2, L1.1, R1.1, R2.1, R10.1, SW1.1, U2.3, U3.8
/ENABLE: R9.2, U3.11
/FB: R15.2, RV1.1, U3.14
/LBO: J9.2, R13.2, U3.12
/MISO: D3.2, J13.2, U5.6
/MOSI: J5.2, J11.3, J11.4, J13.3, R7.1, R19.1, U5.5
/RST: J13.6, R14.2, U5.1
/SCK: J5.1, J11.1, J11.2, J13.4, R6.1, R18.1, U5.7
/Status_Battery: D1.1, D2.2, U2.1, U5.2
GND: C2.2, C3.2, C4.2, C5.2, C8.2, C9.2, C10.2, C11.2, J1.1, J1.2, J1.3, J1.4, J1.A1, J1.A12, J1.B1, J1.B12, J7.2, J8.1, J9.3, J10.2, J11.7, J11.8, J12.2, J13.5, R4.1, R5.2, R8.1, R11.2, R12.1, R17.1, RV1.2, SW1.3, U1.4, U2.2, U3.5, U3.6, U3.7, U3.10, U3.13, U3.17, U4.1, U5.4
unnamed: C1.1, R1.2, U1.8
unnamed: C1.2, J2.1, JP3.2, R4.2, U1.5, U1.6
unnamed: C2.1, J1.A4, J1.A9, J1.B4, J1.B9, R3.2, TP1.1, U2.4
unnamed: C6.1, R20.1, U6.5
unnamed: C6.2, J14.1, U6.6, U7.3
unnamed: D1.2, R3.1
unnamed: D2.1, R5.1
unnamed: D3.1, R12.2
unnamed: D4.1, R17.2
unnamed: J14.2, J16.1, JP2.1, R20.2
unnamed: J15.1, U5.3
unnamed: J17.1, JP3.1, R21.1, U7.1
unnamed: JP1.2, R18.2, R19.2
unnamed: L1.2, U3.3, U3.4
unnamed: R2.2, U1.7
unnamed: R6.2, U1.1
unnamed: R7.2, U1.2
unnamed: R8.2, U2.5
unnamed: R9.1, SW1.2
unnamed: R10.2, R11.1, U3.9
unnamed: R21.2, U6.2
unnamed: TP2.1, U6.1, U7.4
unnamed: TP3.1, U6.3, U7.2
unnamed: U7.5, U7.6, U7.7, U7.8
